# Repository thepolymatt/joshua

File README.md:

# joshua
The Repository for "Joshua" the audio/OSD mod for CRT TVs

Full readme coming soon!

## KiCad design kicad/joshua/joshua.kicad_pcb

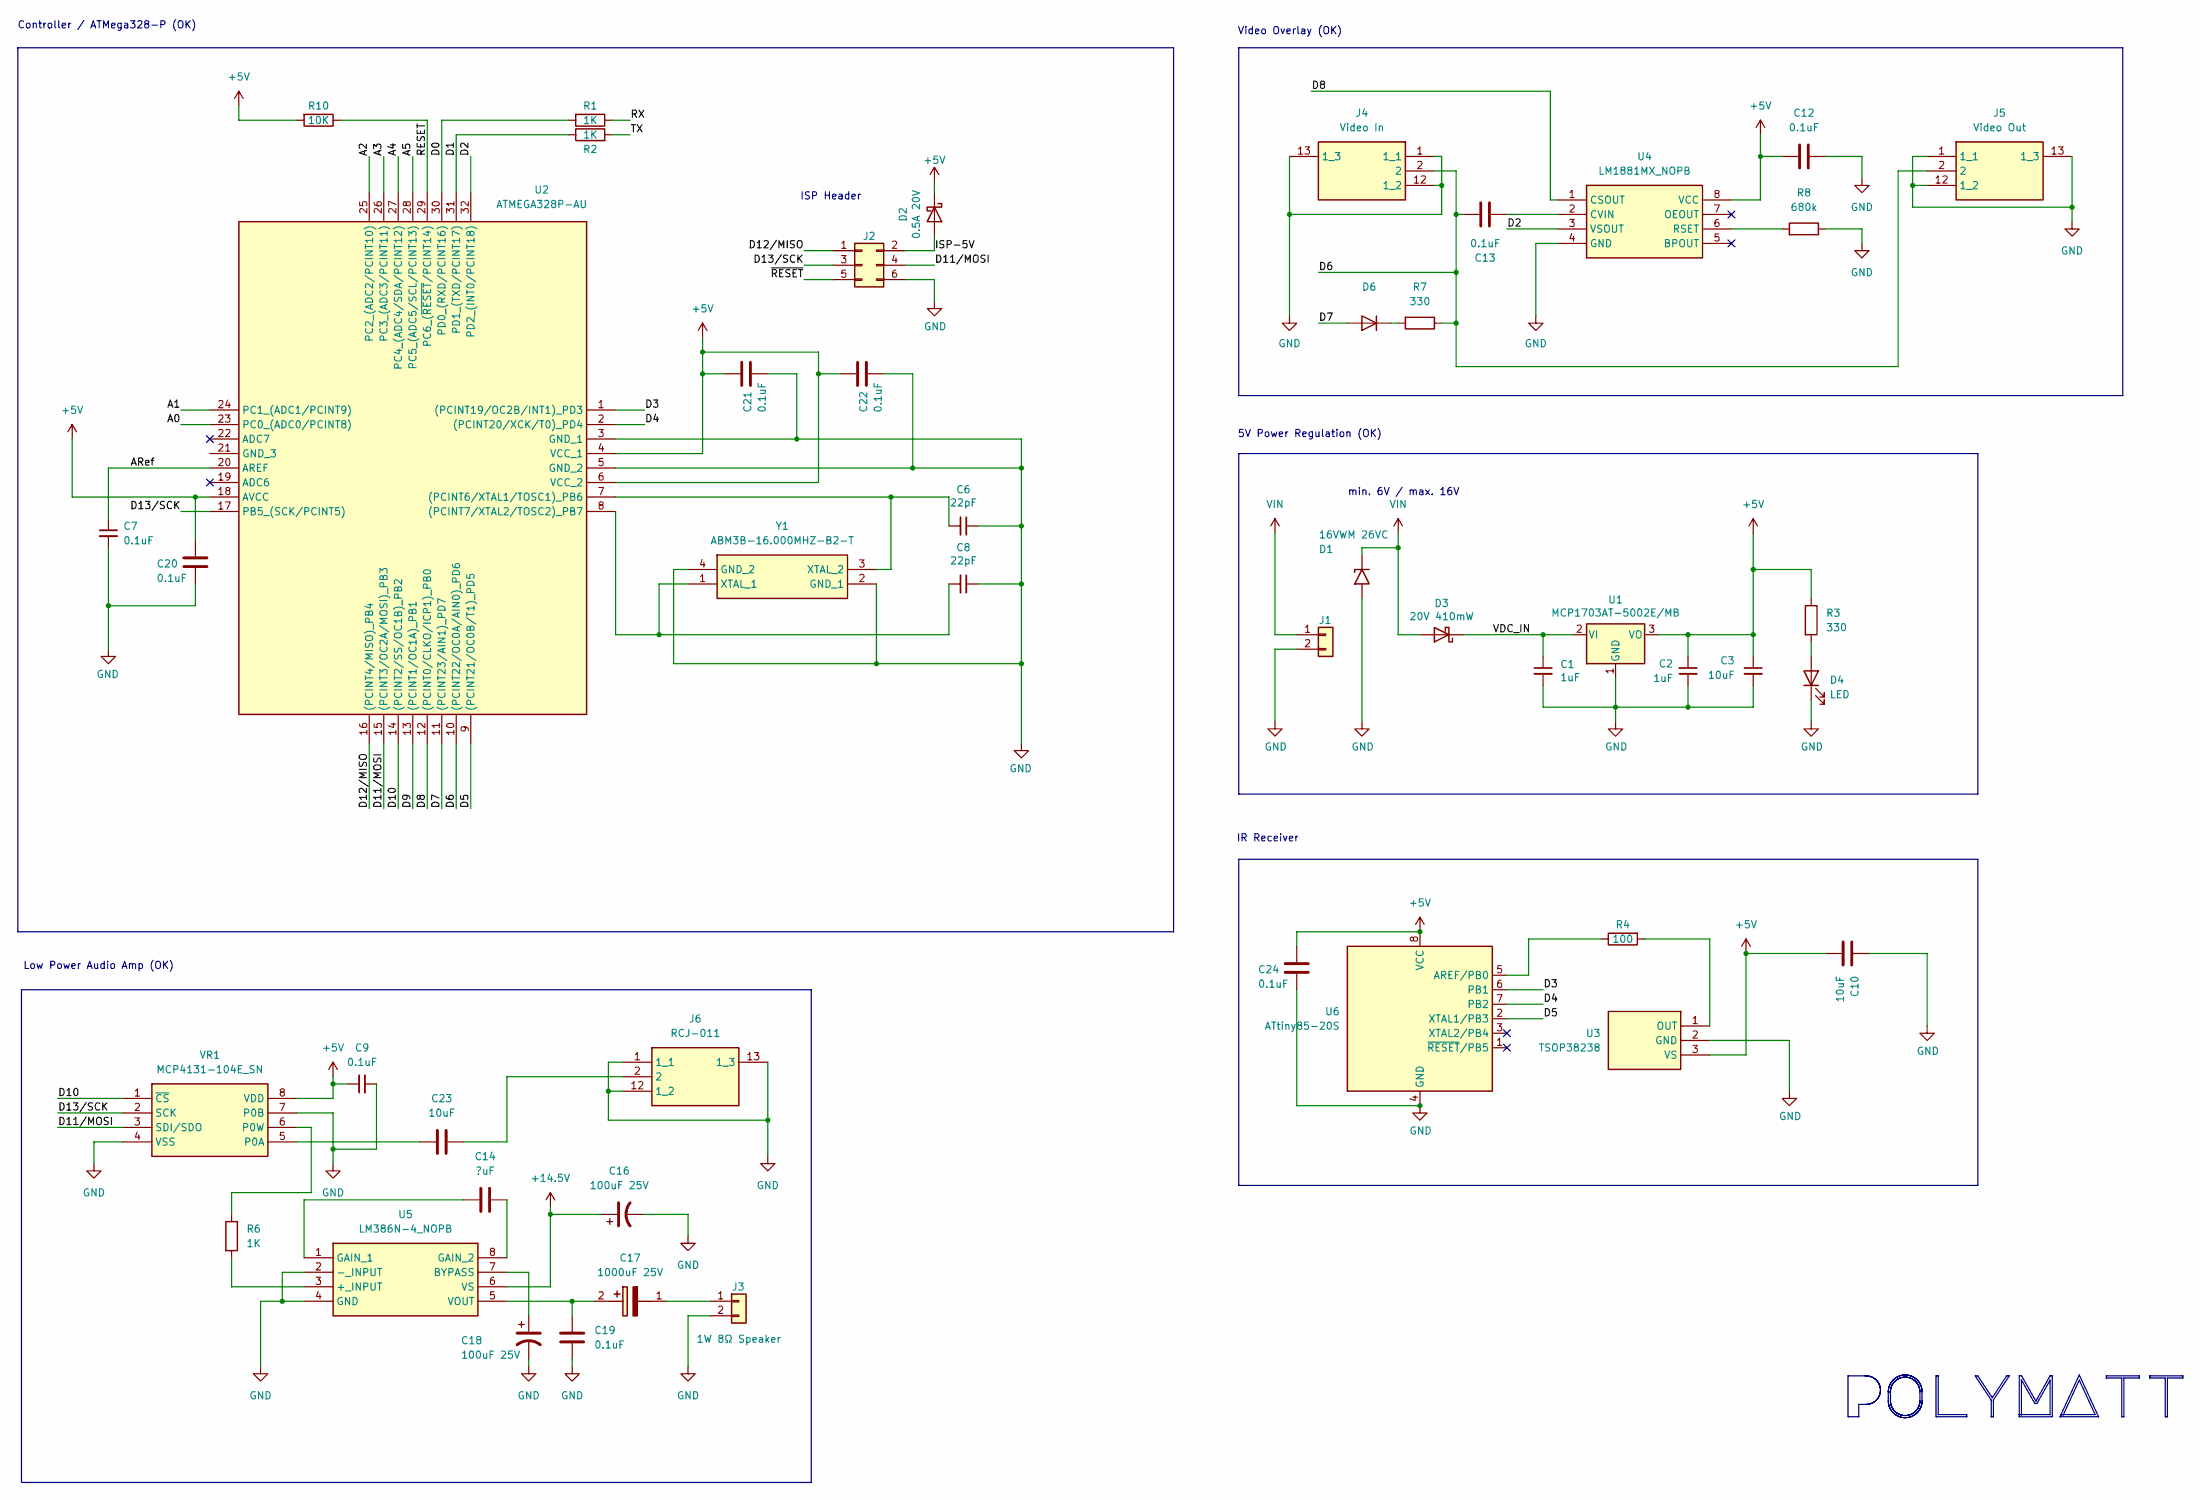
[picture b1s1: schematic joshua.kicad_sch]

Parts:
C1, C2: 1uF; C_0805_2012Metric_Pad1.18x1.45mm_HandSolder; Mouser Part Number 80-C0805C105K3RECTU
C3, C10, C23: 10uF; C_0805_2012Metric_Pad1.18x1.45mm_HandSolder; Mouser Part Number 80-C0805C106M3PACLR
C6, C8: 22pF; C_0805_2012Metric_Pad1.18x1.45mm_HandSolder; Mouser Part Number 80-C0805C220J3HAUTO
C7, C9, C12, C13, C19, C20, C21, C22, C24: 0.1uF; C_0805_2012Metric_Pad1.18x1.45mm_HandSolder; Mouser Part Number 80-C0805C104J3REAULR
C14: ?uF; C_0805_2012Metric_Pad1.18x1.45mm_HandSolder; Mouser Part Number 80-C0805C106M3PACLR
C16, C18: 100uF 25V; CAPAE830X650N; Manufacturer_Part_Number 865090449009; Mouser Part Number 710-865090449009
C17: 1000uF 25V; CAPAE1350X1400N; Mouser Part Number 710-865060462010
D1: 16VWM 26VC; D_SMA; Manufacturer_Part_Number SMAJ16A; Mouser Part Number 652-SMAJ16A
D2: 0.5A 20V; D_SOD-123; Mouser Part Number 863-MBR0520LT3G
D3: 20V 410mW; D_SOD-123; Mouser Part Number 621-B0520LW-F
D4: LED; LED_0805_2012Metric_Pad1.15x1.40mm_HandSolder; Mouser Part Number 593-LSM0805543V
D6: 100V, 200mA; D_SOD-123; Manufacturer_Part_Number 1N4148W-7-F; Mouser Part Number 621-1N4148W-F
J1, J3: Conn_01x02; JST_XH_B2B-XH-AM_1x02_P2.50mm_Vertical
J2: Conn_02x03_Odd_Even; IDC-Header_2x03_P2.54mm_Vertical
J4: Video In; RCJ011; Mouser Part Number 490-RCJ-011
J5: Video Out; RCJ011; Mouser Part Number 490-RCJ-011
J6: RCJ-011; RCJ011; Mouser Part Number 490-RCJ-011
R1, R2, R6: 1K; R_0805_2012Metric_Pad1.20x1.40mm_HandSolder; Mouser Part Number 667-ERA-6AED102V
R3, R7: 330; R_0805_2012Metric_Pad1.20x1.40mm_HandSolder; Mouser Part Number 667-ERA-6VEB3300V
R4: 100; R_0805_2012Metric_Pad1.20x1.40mm_HandSolder; Mouser Part Number 667-ERJ-P06D1000V
R8: 680k; R_0805_2012Metric_Pad1.20x1.40mm_HandSolder; Mouser Part Number 667-ERJ-S06F6803V
R10: 10K; R_0805_2012Metric_Pad1.20x1.40mm_HandSolder; Mouser Part Number 667-ERA-6AED102V
U1: MCP1703AT-5002E/MB; SOT-89-3; Mouser Part Number 579-MCP1703AT5002EMB
U2: ATMEGA328P-AU; QFP80P900X900X120-32N; Mouser Part Number 556-ATMEGA328P-AU
U3: TSOP38238; Mouser Part Number 782-TSOP38238
U4: LM1881MX_NOPB; SOIC127P600X175-8N; Manufacturer_Part_Number LM1881MX/NOPB; Mouser Part Number 926-LM1881MX/NOPB
U5: LM386N-4_NOPB; DIP794W53P254L959H508Q8N; Mouser Part Number 926-LM386N-4/NOPB
U6: ATtiny85-20S; SOIC-8_5.3x5.3mm_P1.27mm
VR1: MCP4131-104E_SN; SOIC127P600X175-8N; Mouser Part Number 579-MCP4131-104E/SN
Y1: ABM3B-16.000MHZ-B2-T; ABM3B; Mouser Part Number 815-ABM3B-12-B2

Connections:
+5V: C2.1, C3.1, C9.1, C10.2, C12.2, C20.1, C21.1, C22.1, C24.1, D2.1 (K), R3.1, R10.2, U1.3 (VO), U2.4 (VCC_1), U2.6 (VCC_2), U2.18 (AVCC), U3.3 (VS), U4.8 (VCC), U6.8 (VCC), VR1.8 (VDD)
/A0: U2.23 (PC0_(ADC0/PCINT8))
/A1: U2.24 (PC1_(ADC1/PCINT9))
/A2: U2.25 (PC2_(ADC2/PCINT10))
/A3: U2.26 (PC3_(ADC3/PCINT11))
/A4: U2.27 (PC4_(ADC4/SDA/PCINT12))
/A5: U2.28 (PC5_(ADC5/SCL/PCINT13))
/ARef: C7.1, U2.20 (AREF)
/D0: R1.2, U2.30 (PD0_(RXD/PCINT16))
/D1: R2.1, U2.31 (PD1_(TXD/PCINT17))
/D2: U2.32 (PD2_(INT0/PCINT18)), U4.3 (VSOUT)
/D3: U2.1 ((PCINT19/OC2B/INT1)_PD3), U6.6 (PB1)
/D4: U2.2 ((PCINT20/XCK/T0)_PD4), U6.7 (PB2)
/D5: U2.9 ((PCINT21/OC0B/T1)_PD5), U6.2 (XTAL1/PB3)
/D6: C13.1, J4.2, J5.2, R7.1, U2.10 ((PCINT22/OC0A/AIN0)_PD6)
/D7: D6.2 (A), U2.11 ((PCINT23/AIN1)_PD7)
/D8: U2.12 ((PCINT0/CLKO/ICP1)_PB0), U4.1 (CSOUT)
/D9: U2.13 ((PCINT1/OC1A)_PB1)
/D10: U2.14 ((PCINT2/SS/OC1B)_PB2), VR1.1 (~CS)
/D11/MOSI: J2.4, U2.15 ((PCINT3/OC2A/MOSI)_PB3), VR1.3 (SDI/SDO); also elsewhere on the board
/D12/MISO: J2.1, U2.16 ((PCINT4/MISO)_PB4); also elsewhere on the board
/D13/SCK: J2.3, U2.17 (PB5_(SCK/PCINT5)), VR1.2 (SCK); also elsewhere on the board
/ISP-5V: D2.2 (A), J2.2; also elsewhere on the board
/RESET: R10.1, U2.29 (PC6_(~RESET/PCINT14)); also elsewhere on the board
/RX: R1.1
/TX: R2.2
/VDC_IN: C1.1, D3.1 (K), U1.2 (VI)
GND: C1.2, C2.2, C3.2, C6.1, C7.2, C8.1, C9.2, C10.1, C12.1, C16.2, C18.2, C19.2, C20.2, C21.2, C22.2, C24.2, D1.2 (A2), D4.1 (K), J1.2, J2.6, J3.2, J4.1 (1_1), J4.12 (1_2), J4.13 (1_3), J5.1 (1_1), J5.12 (1_2), J5.13 (1_3), J6.1 (1_1), J6.12 (1_2), J6.13 (1_3), R8.1, U1.1 (GND), U2.3 (GND_1), U2.5 (GND_2), U3.2 (GND), U4.4 (GND), U5.2 (-_INPUT), U5.4 (GND), U6.4 (GND), VR1.4 (VSS), VR1.7 (P0B), Y1.2 (GND_1), Y1.4 (GND_2); also elsewhere on the board
unnamed: C17.2 (+), C19.1, U5.5 (VOUT)
unnamed: C17.1 (-), J3.1
unnamed: C23.1, J6.2
unnamed: D4.2 (A), R3.2
unnamed: D6.1 (K), R7.2
unnamed: C6.2, U2.7 ((PCINT6/XTAL1/TOSC1)_PB6), Y1.3 (XTAL_2)
unnamed: C8.2, U2.8 ((PCINT7/XTAL2/TOSC2)_PB7), Y1.1 (XTAL_1)
unnamed: R4.2, U3.1 (OUT)
unnamed: C13.2, U4.2 (CVIN)
unnamed: R8.2, U4.6 (RSET)
unnamed: R6.2, U5.3 (+_INPUT)
unnamed: C18.1, U5.7 (BYPASS)
unnamed: C14.2, U5.1 (GAIN_1)
unnamed: C14.1, U5.8 (GAIN_2)
unnamed: R4.1, U6.5 (AREF/PB0)
unnamed: C23.2, VR1.5 (P0A)
unnamed: R6.1, VR1.6 (P0W)

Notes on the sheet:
Controller / ATMega328-P (OK)
5V Power Regulation (OK)
min. 6V / max. 16V
ISP Header
Video Overlay (OK)
IR Receiver
Low Power Audio Amp (OK)

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
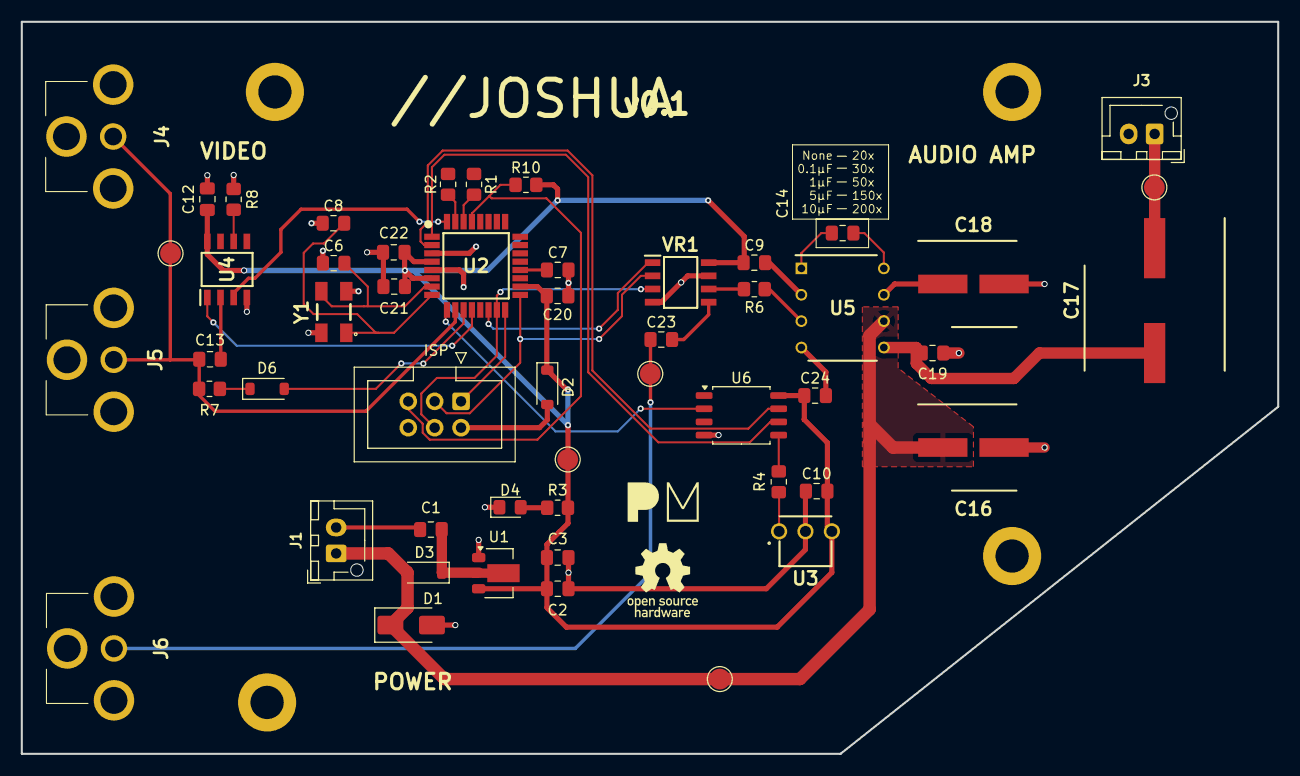
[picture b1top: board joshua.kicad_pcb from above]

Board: 2 copper layers, 121.0 x 70.5 mm, 47 parts (0 on the bottom side), 37 nets.

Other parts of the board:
ISP: Conn_02x03_Odd_Even; IDC-Header_2x03_P2.54mm_Vertical

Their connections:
/D11/MOSI: ISP.4; also elsewhere on the board
/D12/MISO: ISP.1; also elsewhere on the board
/D13/SCK: ISP.3; also elsewhere on the board
/ISP-5V: ISP.2; also elsewhere on the board
/RESET: ISP.5; also elsewhere on the board
GND: ISP.6; also elsewhere on the board

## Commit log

2025-05-24 Initial commit.
2025-05-24 Remove macOS metadata files
2025-05-24 Removed hidden mac files
2025-05-24 Removed hidden files.
